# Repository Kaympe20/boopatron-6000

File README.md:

# The Boopatron 6000

Press the nozzle to see the eyes glow and motors run

[Welcome to the boop zone, population you](https://youtube.com/shorts/GtiIQLBaxNE?si=7qtAsv7QoQyYvnxd)

Slack Username: @Kayla
Slack ID: `U07HY92M9GA`

## Bill of Materials
- 5mm LED x2
- CR2032 battery cell x1
- 220Ω resistors x2
- mini motor disc x1
- 6mm push button x1

# Pics
(The edge cuts was causing errors in KiCAD, but things like JLCPCB can use it)

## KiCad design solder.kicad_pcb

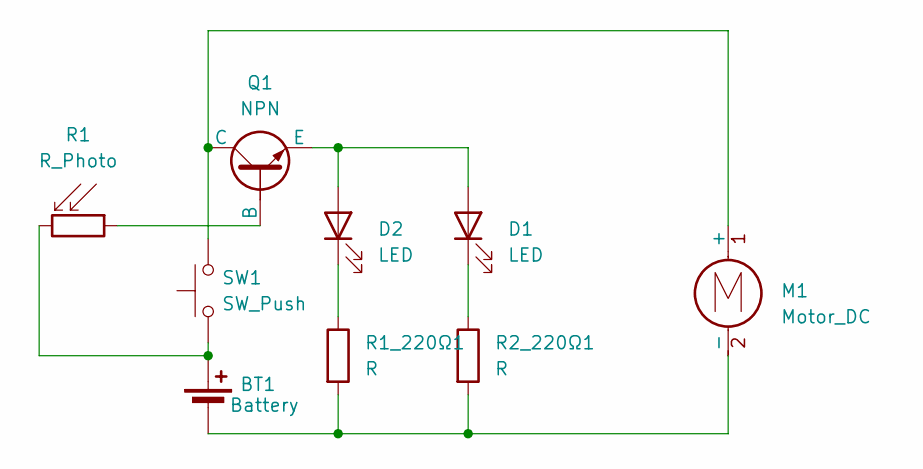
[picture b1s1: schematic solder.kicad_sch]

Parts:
BT1: Battery; BatteryHolder_Keystone_3034_1x20mm
D1, D2: LED; LED_D5.0mm
M1: Motor_DC; PinHeader_1x02_P2.54mm_Vertical
Q1: NPN; TO-92L_HandSolder
R1: R_Photo; R_LDR_5.1x4.3mm_P3.4mm_Vertical
R1_220Ω1, R2_220Ω1: R; R_Axial_DIN0207_L6.3mm_D2.5mm_P7.62mm_Horizontal
SW1: SW_Push; SW_PUSH_6mm

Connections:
unnamed: BT1.1 (+), R1.2, SW1.1
unnamed: BT1.2 (-), M1.2 (-), R1_220Ω1.2, R2_220Ω1.2
unnamed: D1.2 (A), D2.2 (A), Q1.3 (E)
unnamed: D1.1 (K), R2_220Ω1.1
unnamed: D2.1 (K), R1_220Ω1.1
unnamed: M1.1 (+), Q1.1 (C), SW1.2
unnamed: Q1.2 (B), R1.1

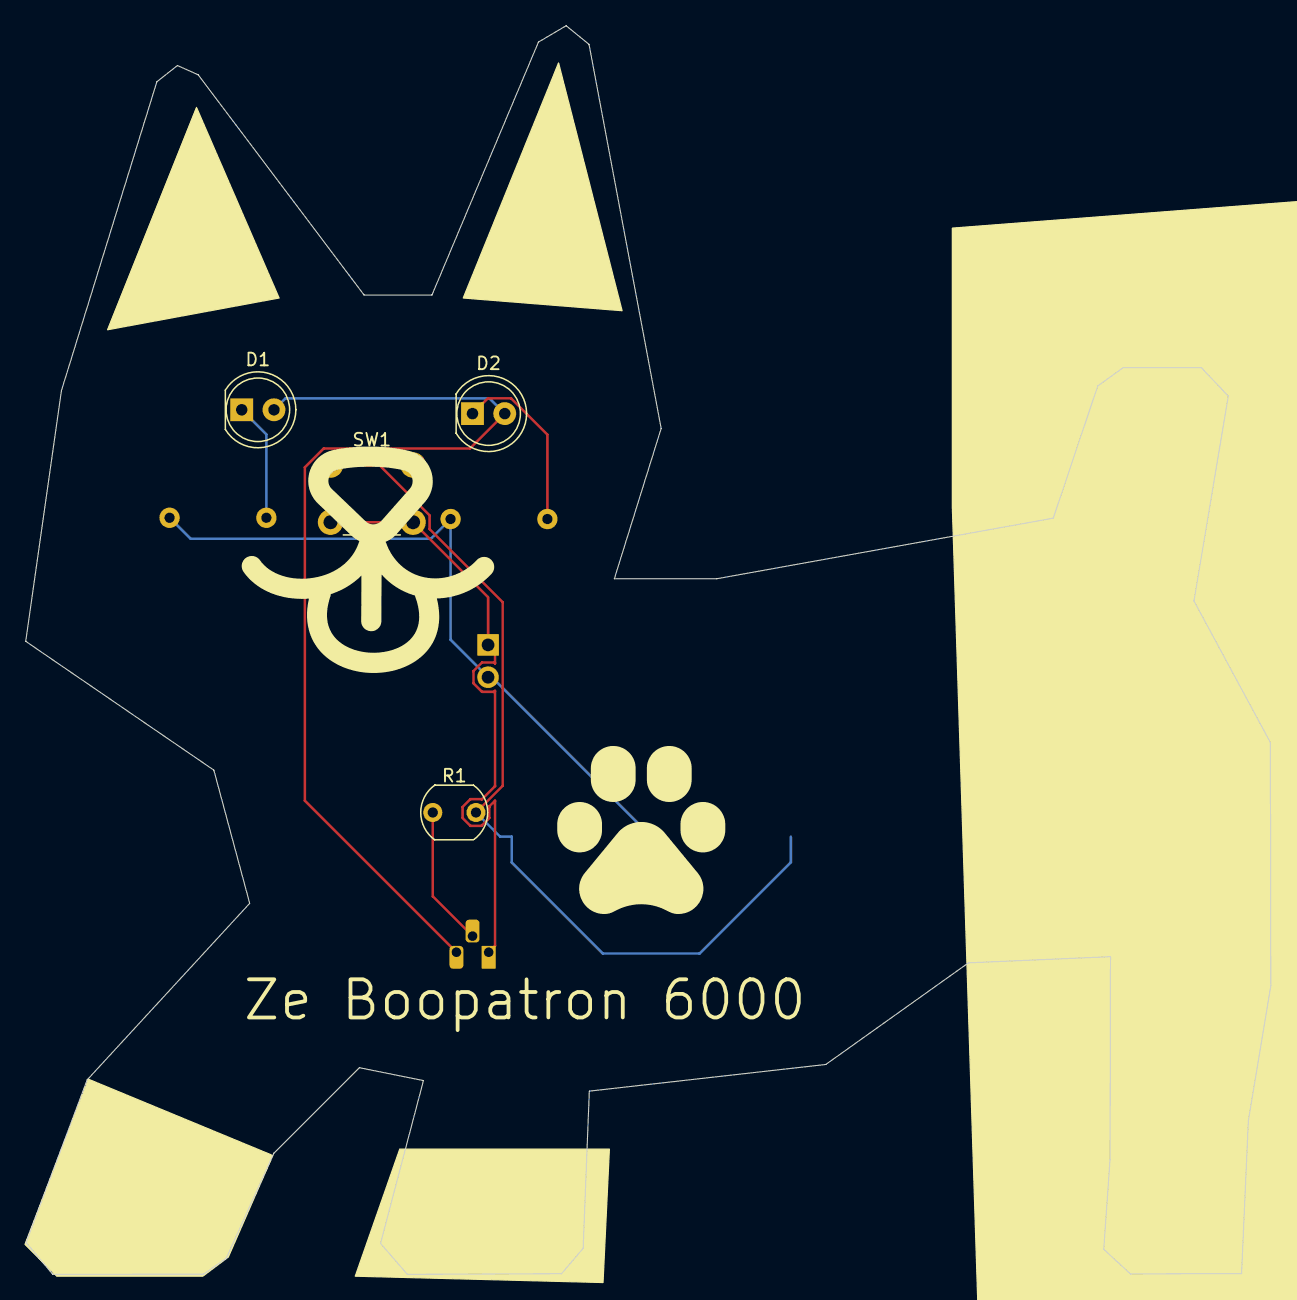
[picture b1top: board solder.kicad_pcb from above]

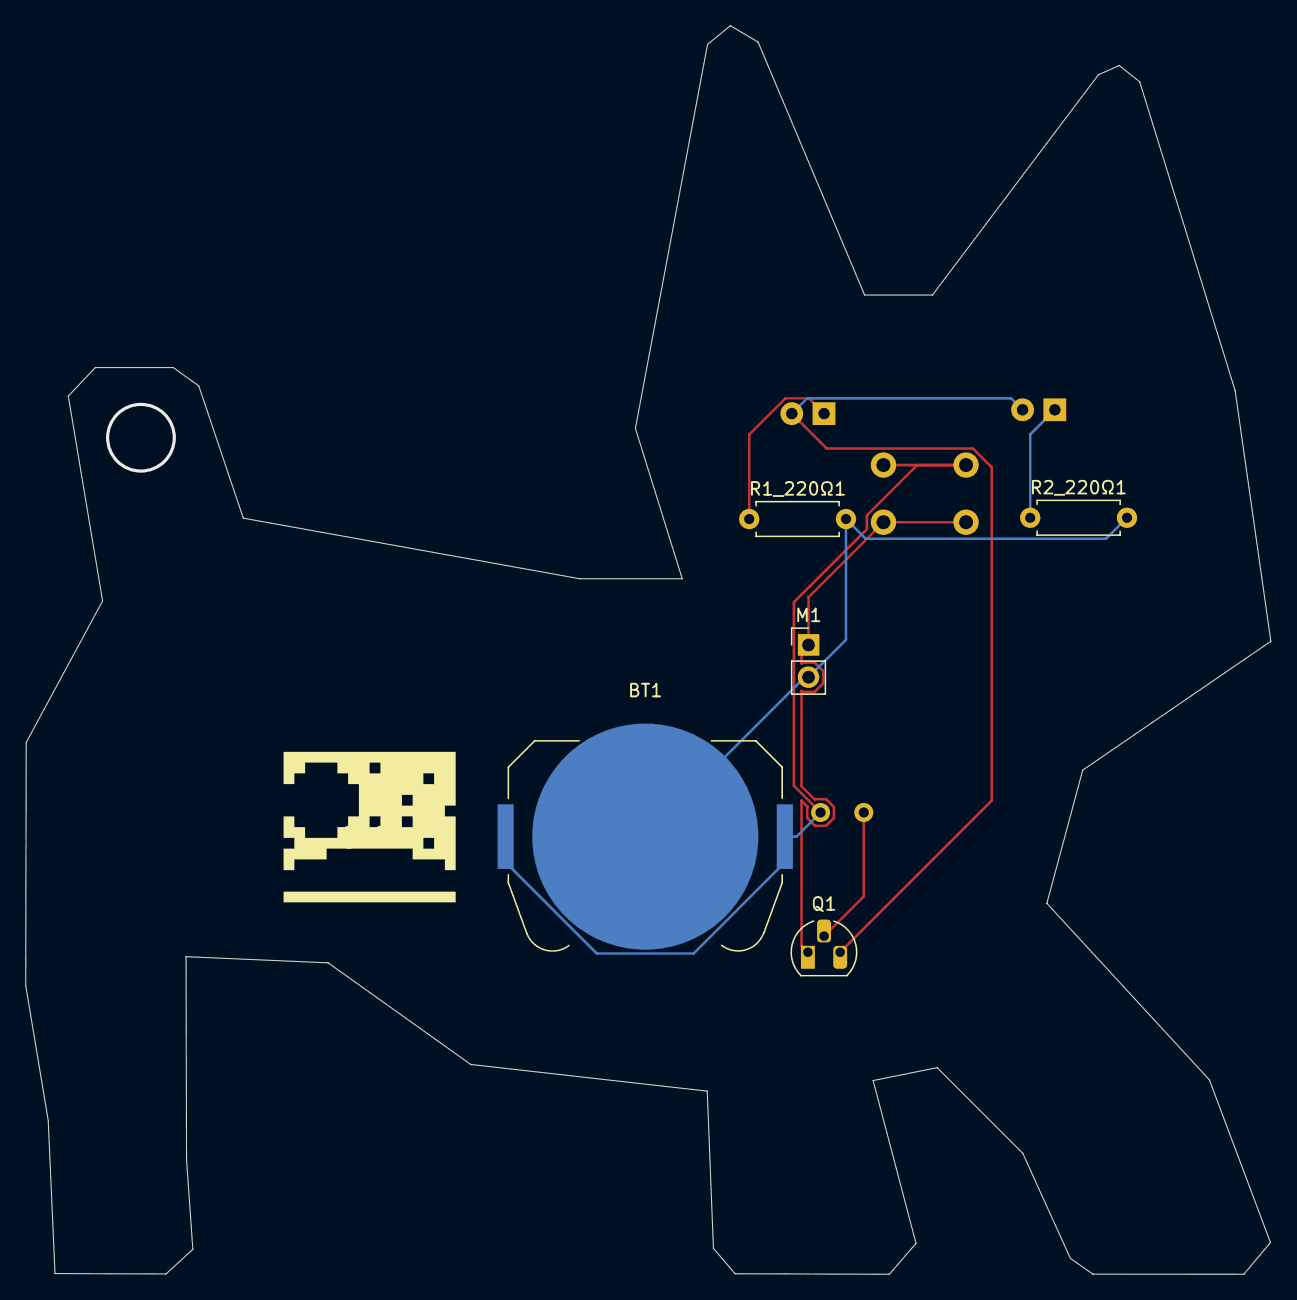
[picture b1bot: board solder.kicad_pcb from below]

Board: 2 copper layers, 98.0 x 98.3 mm, 9 parts (5 on the bottom side), 7 nets.

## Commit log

2025-08-08 Fix edge cuts
2025-08-14 Add more silkscreen art
2025-08-15 Add gitignore
2025-08-15 Make more complex including photoresistor and transistor
